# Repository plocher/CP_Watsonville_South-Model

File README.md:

# CP_Watsonville_South-Model
## License: CERN Open Hardware Licence v1.2

Model Board for CP Watsonville South - Maintainer Sevice Panel

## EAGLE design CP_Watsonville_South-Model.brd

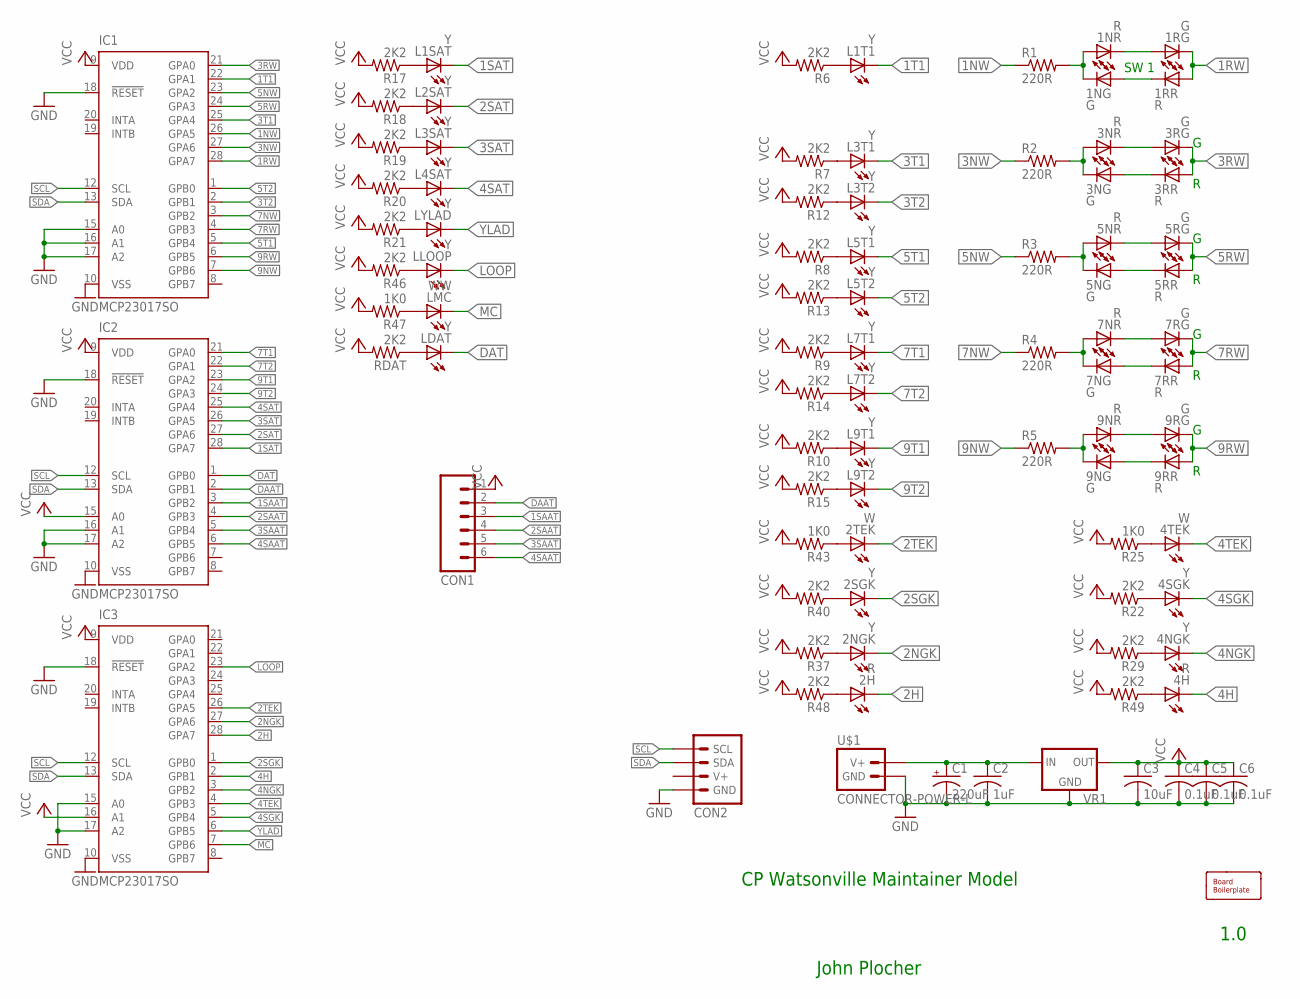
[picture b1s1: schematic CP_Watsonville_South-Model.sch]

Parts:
1NG, 1RG, 3NG, 3RG, 5NG, 5RG, 7NG, 7RG, 9NG, 9RG: G; 0603-LED
1NR, 1RR, 2H, 3NR, 3RR, 4H, 5NR, 5RR, 7NR, 7RR, 9NR, 9RR: R; 0603-LED
2NGK, 2SGK, 4NGK, 4SGK: Y; 0603-LED
2TEK, 4TEK: W; 0603-LED
BOARD1: BOARD100X150; BOARD-SEEED10X15
C1: 220uF; 0810-CAP
C2: 1uF; 0603-CAP
C3: 10uF; 0603-CAP
C4, C5, C6: 0.1uF; 0603-CAP
CON1: CONNECTOR-M06LOCK; 1X06_LOCK
CON2: CONNECTOR-I2CNOOUTLINE; I2C-NOOUTLINE
IC1, IC2, IC3: MCP23017SO; SO28W
L1SAT, L1T1, L2SAT, L3SAT, L3T1, L3T2, L4SAT, L5T1, L5T2, L7T1, L7T2, L9T1, L9T2: Y; 0603-LED
LDAT: Y; 0603-LED
LLOOP: Y; 0603-LED
LMC: WW; 0603-LED
LYLAD: Y; 0603-LED
R1, R2, R3, R4, R5: 220R; 0603-RES
R6, R7, R8, R9, R10, R12, R13, R14, R15, R17, R18, R19, R20, R21, R22, R29, R37, R40, R46, R48, R49: 2K2; 0603-RES
R25, R43, R47: 1K0; 0603-RES
RDAT: 2K2; 0603-RES
U$1: CONNECTOR-POWER-L; POWER-R2
VR1: VREG-DPAK-5; TO-252

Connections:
1NW: IC1.26 (GPA5), R1.1
1RW: 1RG.C, 1RR.A, IC1.28 (GPA7)
1SAAT: CON1.3, IC2.3 (GPB2)
1SAT: IC2.28 (GPA7), L1SAT.C
1T1: IC1.22 (GPA1), L1T1.C
2H: 2H.C, IC3.28 (GPA7)
2NGK: 2NGK.C, IC3.27 (GPA6)
2SAAT: CON1.4, IC2.4 (GPB3)
2SAT: IC2.27 (GPA6), L2SAT.C
2SGK: 2SGK.C, IC3.1 (GPB0)
2TEK: 2TEK.C, IC3.26 (GPA5)
3NW: IC1.27 (GPA6), R2.1
3RW: 3RG.C, 3RR.A, IC1.21 (GPA0)
3SAAT: CON1.5, IC2.5 (GPB4)
3SAT: IC2.26 (GPA5), L3SAT.C
3T1: IC1.25 (GPA4), L3T1.C
3T2: IC1.2 (GPB1), L3T2.C
4H: 4H.C, IC3.2 (GPB1)
4NGK: 4NGK.C, IC3.3 (GPB2)
4SAAT: CON1.6, IC2.6 (GPB5)
4SAT: IC2.25 (GPA4), L4SAT.C
4SGK: 4SGK.C, IC3.5 (GPB4)
4TEK: 4TEK.C, IC3.4 (GPB3)
5NW: IC1.23 (GPA2), R3.1
5RW: 5RG.C, 5RR.A, IC1.24 (GPA3)
5T1: IC1.5 (GPB4), L5T1.C
5T2: IC1.1 (GPB0), L5T2.C
7NW: IC1.3 (GPB2), R4.1
7RW: 7RG.C, 7RR.A, IC1.4 (GPB3)
7T1: IC2.21 (GPA0), L7T1.C
7T2: IC2.22 (GPA1), L7T2.C
9NW: IC1.7 (GPB6), R5.1
9RW: 9RG.C, 9RR.A, IC1.6 (GPB5)
9T1: IC2.23 (GPA2), L9T1.C
9T2: IC2.24 (GPA3), L9T2.C
DAAT: CON1.2, IC2.2 (GPB1)
DAT: IC2.1 (GPB0), LDAT.C
GND: C1.-, C2.2, C3.2, C4.2, C5.2, C6.2, CON2.GND, IC1.10 (VSS), IC1.15 (A0), IC1.16 (A1), IC1.17 (A2), IC1.18 (!RESET), IC2.10 (VSS), IC2.16 (A1), IC2.17 (A2), IC2.18 (!RESET), IC3.10 (VSS), IC3.15 (A0), IC3.17 (A2), IC3.18 (!RESET), U$1.GND, U$1.GND@1 (GND), U$1.GND@2 (GND), U$1.GND@3 (GND), VR1.2 (GND)
LOOP: IC3.23 (GPA2), LLOOP.C
MC: IC3.7 (GPB6), LMC.C
unnamed: 3NR.C, 3RG.A
unnamed: 3NG.A, 3RR.C
unnamed: 1NG.C, 1NR.A, R1.2
unnamed: L1T1.A, R6.1
unnamed: L3T1.A, R7.1
unnamed: 3NG.C, 3NR.A, R2.2
unnamed: 5NG.C, 5NR.A, R3.2
unnamed: 7NG.C, 7NR.A, R4.2
unnamed: 9NG.C, 9NR.A, R5.2
unnamed: L5T1.A, R8.1
unnamed: L7T1.A, R9.1
unnamed: L9T1.A, R10.1
unnamed: 1NR.C, 1RG.A
unnamed: L3T2.A, R12.1
unnamed: L5T2.A, R13.1
unnamed: L7T2.A, R14.1
unnamed: L9T2.A, R15.1
unnamed: LDAT.A, RDAT.1
unnamed: L1SAT.A, R17.1
unnamed: L2SAT.A, R18.1
unnamed: L3SAT.A, R19.1
unnamed: L4SAT.A, R20.1
unnamed: LYLAD.A, R21.1
unnamed: 4SGK.A, R22.1
unnamed: 1NG.A, 1RR.C
unnamed: 5NR.C, 5RG.A
unnamed: 4TEK.A, R25.1
unnamed: 5NG.A, 5RR.C
unnamed: 7NR.C, 7RG.A
unnamed: 7NG.A, 7RR.C
unnamed: 4NGK.A, R29.1
unnamed: 9NR.C, 9RG.A
unnamed: 9NG.A, 9RR.C
unnamed: 2NGK.A, R37.1
unnamed: 2SGK.A, R40.1
unnamed: 2TEK.A, R43.1
unnamed: LLOOP.A, R46.1
unnamed: LMC.A, R47.1
unnamed: 2H.A, R48.1
unnamed: 4H.A, R49.1
SCL: CON2.SCL, IC1.12 (SCL), IC2.12 (SCL), IC3.12 (SCL)
SDA: CON2.SDA, IC1.13 (SDA), IC2.13 (SDA), IC3.13 (SDA)
VCC: C3.1, C4.1, C5.1, C6.1, CON1.1, IC1.9 (VDD), IC2.9 (VDD), IC2.15 (A0), IC3.9 (VDD), IC3.16 (A1), R6.2, R7.2, R8.2, R9.2, R10.2, R12.2, R13.2, R14.2, R15.2, R17.2, R18.2, R19.2, R20.2, R21.2, R22.2, R25.2, R29.2, R37.2, R40.2, R43.2, R46.2, R47.2, R48.2, R49.2, RDAT.2, VR1.3 (OUT)
VIN: C1.+, C2.1, U$1.V+, U$1.V+@1 (V+), U$1.V+@2 (V+), U$1.V+@3 (V+), VR1.1 (IN)
YLAD: IC3.6 (GPB5), LYLAD.C

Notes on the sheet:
SW 1
CP Watsonville Maintainer Model
1.0
John Plocher

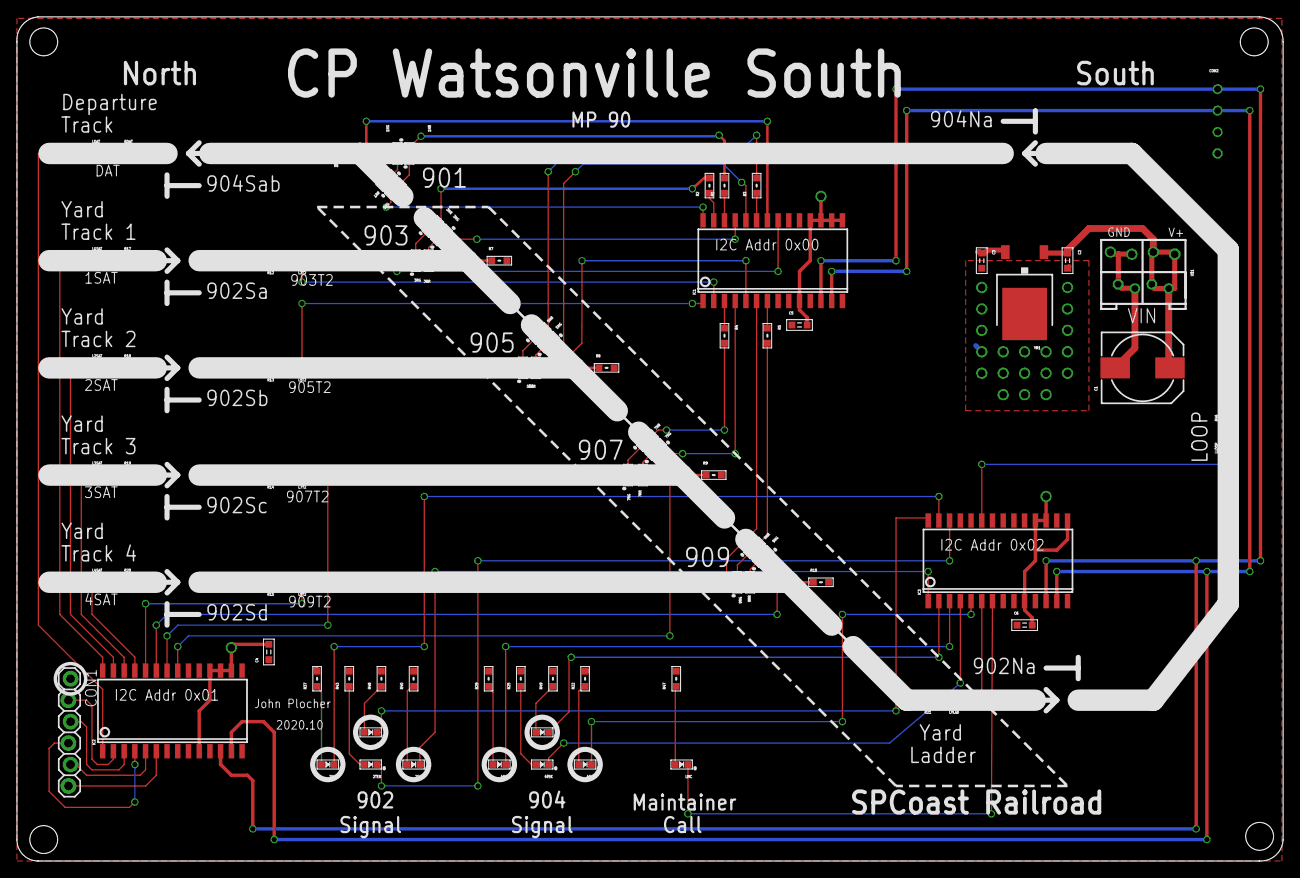
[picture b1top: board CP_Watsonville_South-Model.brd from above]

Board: 2 copper layers, 150.0 x 100.0 mm, 89 parts (0 on the bottom side), 85 nets.

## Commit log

2020-11-03 Initial version
2020-11-03 Added 1x6 for MID-model board
2020-11-03 Added JLC Part number template to back silk
